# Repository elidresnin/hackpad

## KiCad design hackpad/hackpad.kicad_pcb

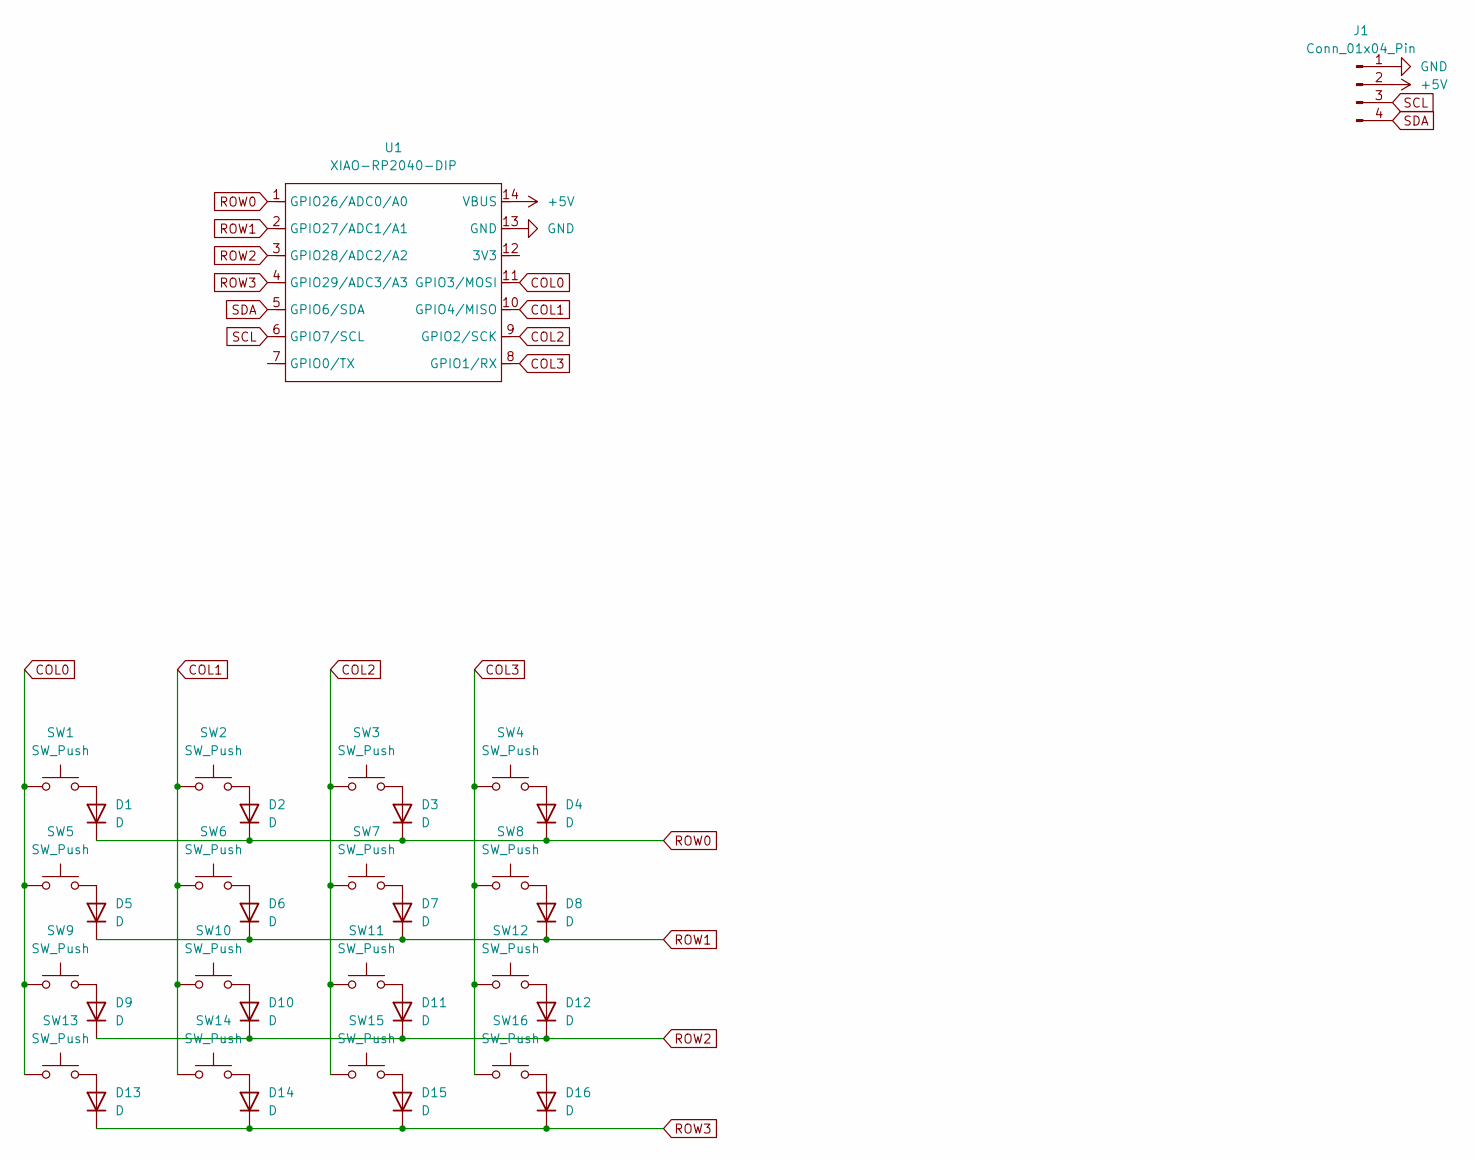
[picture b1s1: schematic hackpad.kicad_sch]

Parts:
D1, D2, D3, D4, D5, D6, D7, D8, D9, D10, D11, D12, D13, D14, D15, D16: D; D_DO-35_SOD27_P7.62mm_Horizontal
J1: Conn_01x04_Pin; SSD1306-0.91-OLED-4pin-128x32
SW1, SW2, SW3, SW4, SW5, SW6, SW7, SW8, SW9, SW10, SW11, SW12, SW13, SW14, SW15, SW16: SW_Push; SW_Cherry_MX_1.00u_PCB
U1: XIAO-RP2040-DIP

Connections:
+5V: J1.2, U1.14 (VBUS)
COL0: SW1.1, SW5.1, SW9.1, SW13.1, U1.11 (GPIO3/MOSI)
COL1: SW2.1, SW6.1, SW10.1, SW14.1, U1.10 (GPIO4/MISO)
COL2: SW3.1, SW7.1, SW11.1, SW15.1, U1.9 (GPIO2/SCK)
COL3: SW4.1, SW8.1, SW12.1, SW16.1, U1.8 (GPIO1/RX)
GND: J1.1, U1.13 (GND)
unnamed: D1.2 (A), SW1.2
unnamed: D2.2 (A), SW2.2
unnamed: D3.2 (A), SW3.2
unnamed: D4.2 (A), SW4.2
unnamed: D5.2 (A), SW5.2
unnamed: D6.2 (A), SW6.2
unnamed: D7.2 (A), SW7.2
unnamed: D8.2 (A), SW8.2
unnamed: D9.2 (A), SW9.2
unnamed: D10.2 (A), SW10.2
unnamed: D11.2 (A), SW11.2
unnamed: D12.2 (A), SW12.2
unnamed: D13.2 (A), SW13.2
unnamed: D14.2 (A), SW14.2
unnamed: D15.2 (A), SW15.2
unnamed: D16.2 (A), SW16.2
ROW0: D1.1 (K), D2.1 (K), D3.1 (K), D4.1 (K), U1.1 (GPIO26/ADC0/A0)
ROW1: D5.1 (K), D6.1 (K), D7.1 (K), D8.1 (K), U1.2 (GPIO27/ADC1/A1)
ROW2: D9.1 (K), D10.1 (K), D11.1 (K), D12.1 (K), U1.3 (GPIO28/ADC2/A2)
ROW3: D13.1 (K), D14.1 (K), D15.1 (K), D16.1 (K), U1.4 (GPIO29/ADC3/A3)
SCL: J1.3, U1.6 (GPIO7/SCL)
SDA: J1.4, U1.5 (GPIO6/SDA)

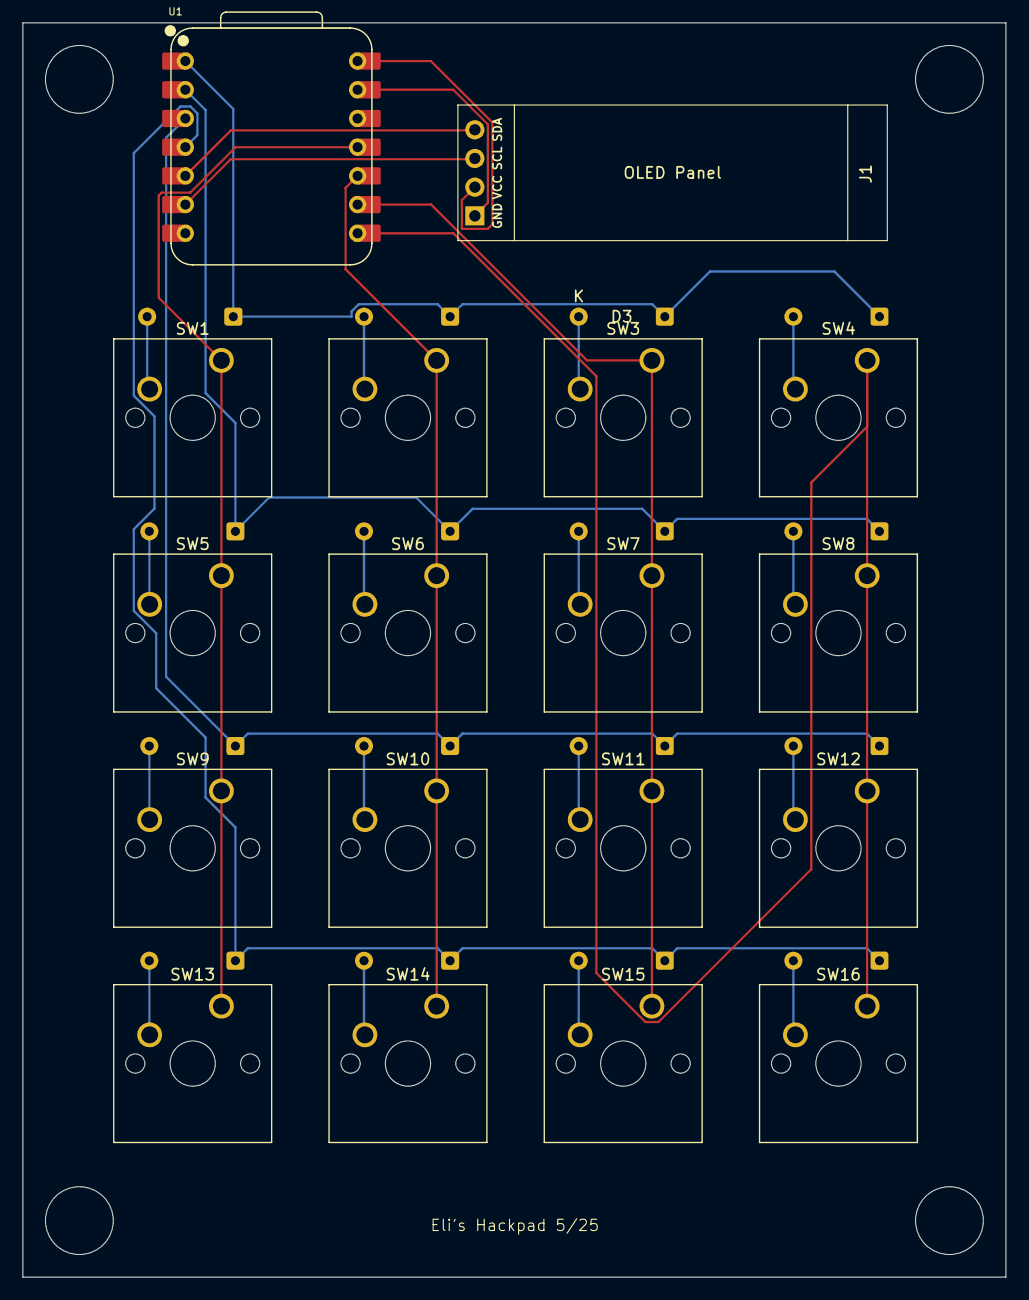
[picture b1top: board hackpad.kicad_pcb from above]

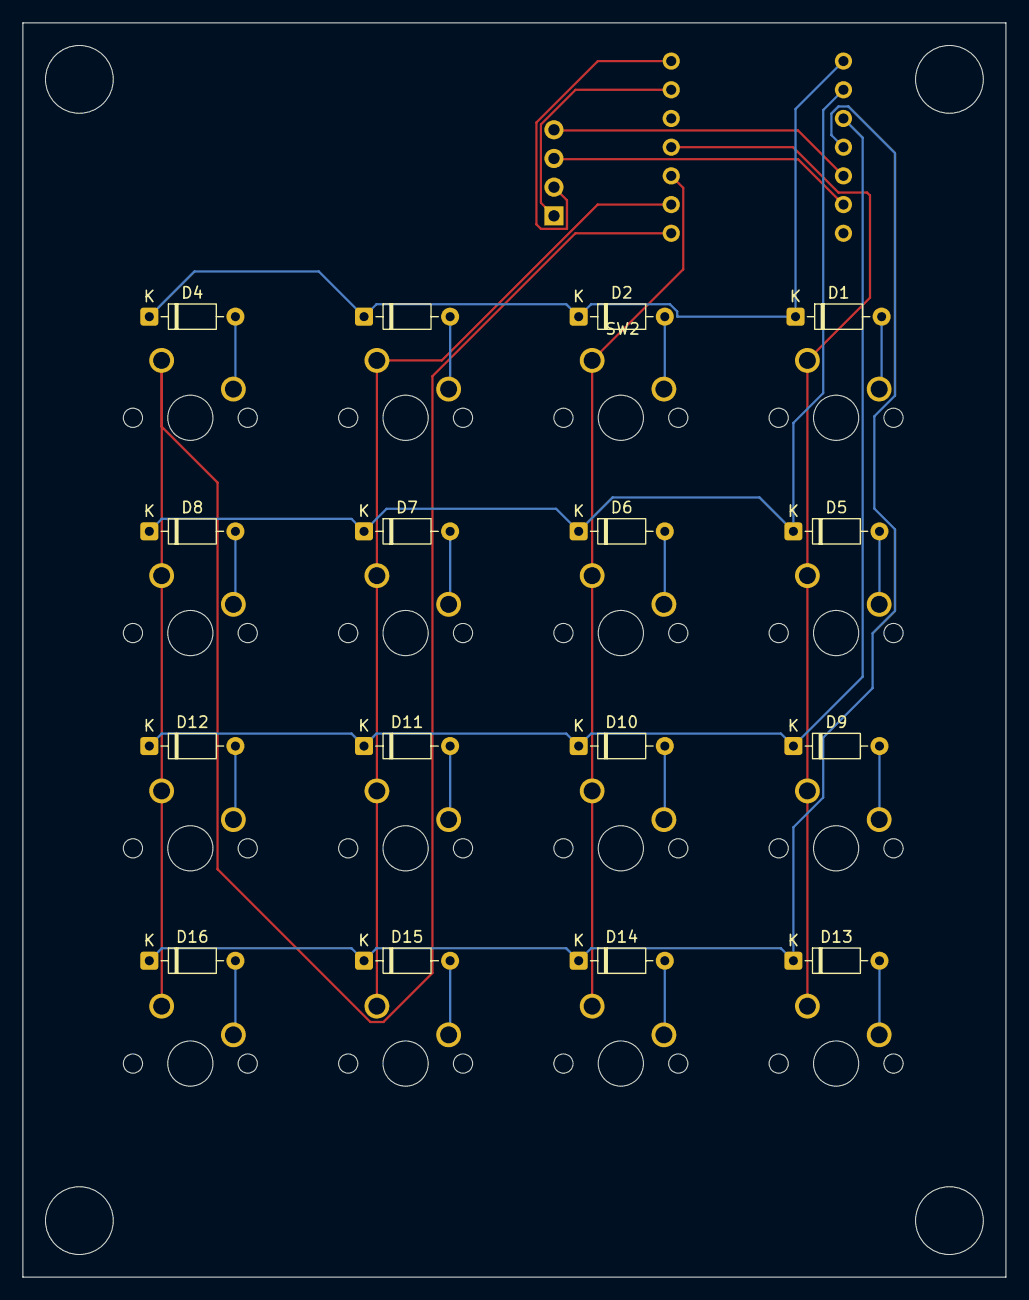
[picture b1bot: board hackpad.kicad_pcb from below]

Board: 2 copper layers, 87.0 x 111.0 mm, 34 parts (16 on the bottom side), 28 nets.

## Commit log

2025-05-23 kicad setup/first schematic
2025-05-23 pcb v1 done
2025-05-23 v2 done?
